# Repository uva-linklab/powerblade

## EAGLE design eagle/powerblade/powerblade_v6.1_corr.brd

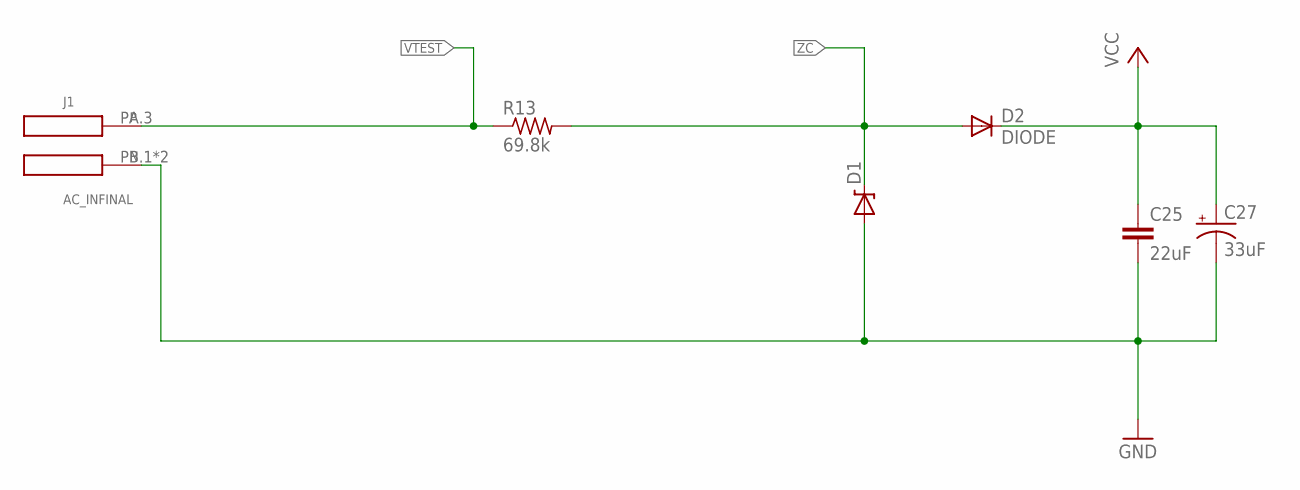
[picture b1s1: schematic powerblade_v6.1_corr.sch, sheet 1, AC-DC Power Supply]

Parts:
C25: 22uF; C0603_SM; DIGIKEY 445-9077-1-ND
C27: 33uF; CPOL0805_SM; DIGIKEY 478-8650-1-ND
D1: ZENERBZT52; BZT52; DIGIKEY BZT52C10T-7DICT-ND
D2: DIODE; BAS521
J1: AC_INFINAL; AC3_FINAL; DIGIKEY ED1649-ND
R13: 69.8k; R1210; DIGIKEY P69.8KAACT-ND

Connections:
GND: C25.2, C27.-, D1.A, J1.PB.1 (N), J1.PB.3 (N); also elsewhere on the board
VCC: C25.1, C27.+, D2.C; also elsewhere on the board
VTEST: J1.PA.3, R13.1; also elsewhere on the board
ZC: D1.C, D2.A, R13.2; also elsewhere on the board

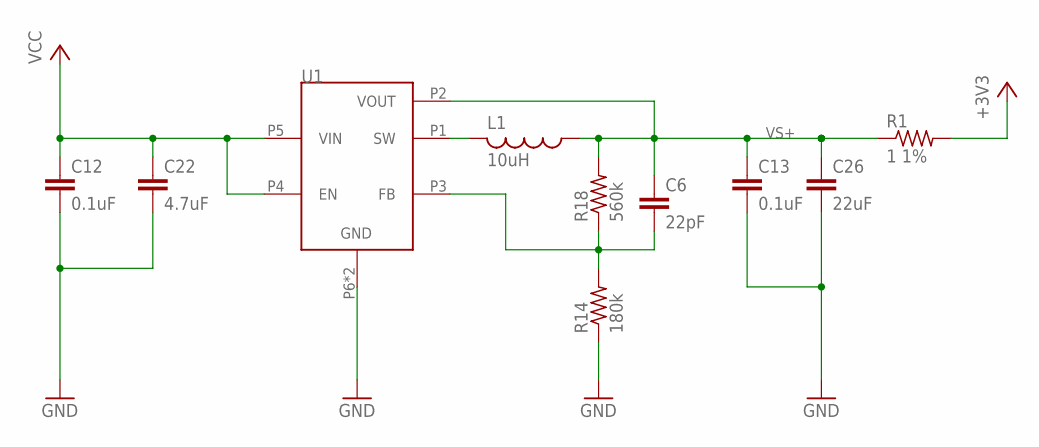
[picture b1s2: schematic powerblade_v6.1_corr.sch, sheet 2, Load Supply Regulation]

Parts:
C6: 22pF; C0402; DIGIKEY 445-1239-1-ND
C12: 0.1uF; C0402; DIGIKEY 445-4952-1-ND
C13: 0.1uF; C0402_SM; DIGIKEY 445-4952-1-ND
C22: 4.7uF; C0402; DIGIKEY 445-8023-1-ND
C26: 22uF; C0603_SM; DIGIKEY 445-9077-1-ND
L1: 10uH; L0805; DIGIKEY 490-4990-1-ND
R1: 1 1%; R0603_SM; DIGIKEY P1.0AJCT-ND
R14: 180k; R0402; DIGIKEY P180KLCT-ND
R18: 560k; R0402; DIGIKEY P560KLCT-ND
U1: TPS62122; WDFN-6

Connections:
+3V3: R1.2; also elsewhere on the board
GND: C12.2, C13.2, C22.2, C26.2, R14.1, U1.P6 (GND), U1.PAD (GND); also elsewhere on the board
unnamed: L1.2, U1.P1 (SW)
unnamed: C6.2, R14.2, R18.1, U1.P3 (FB)
VCC: C12.1, C22.1, U1.P4 (EN), U1.P5 (VIN); also elsewhere on the board
VS+: C6.1, C13.1, C26.1, L1.1, R1.1, R18.2, U1.P2 (VOUT)

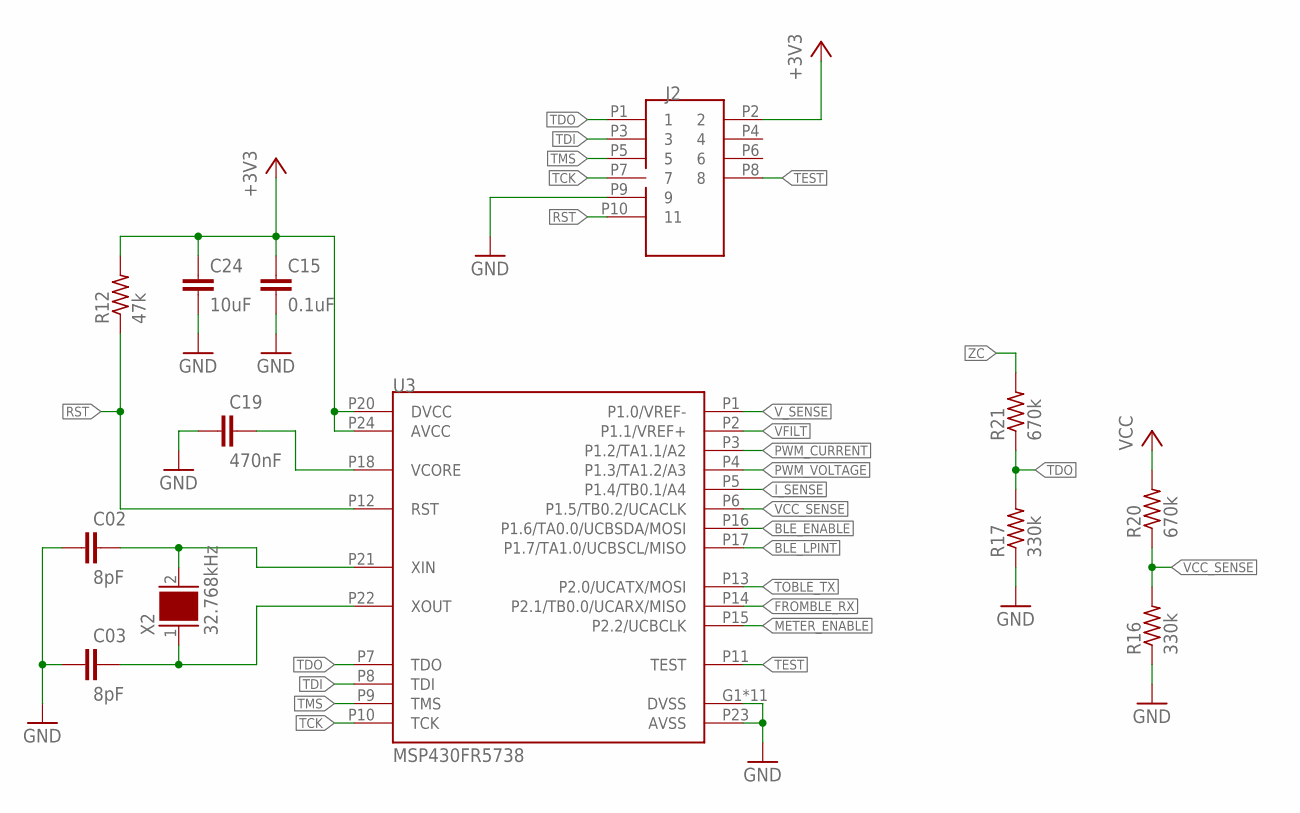
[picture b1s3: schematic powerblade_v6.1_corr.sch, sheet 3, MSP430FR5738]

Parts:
C02, C03: 8pF; C0402; DIGIKEY 445-4890-1-ND
C15: 0.1uF; C0402; DIGIKEY 445-4952-1-ND
C19: 470nF; C0402; DIGIKEY 445-4989-1-ND
C24: 10uF; C0603_SM; DIGIKEY 445-6853-1-ND
J2: JTAG_14PIN_IDC-ND; TC2050-IDC-NL-430-ND; DIGIKEY NP
R12: 47k; R0402; DIGIKEY P47KJCT-ND
R16, R17: 330k; R0402; DIGIKEY P330KLCT-ND
R20, R21: 670k; R0402; DIGIKEY P665KLCT-ND
U3: MSP430FR5738; VQFN-24
X2: 32.768kHz; 0805; DIGIKEY 535-12373-1-ND

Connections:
+3V3: C15.1, C24.1, J2.P2 (2), R12.2, U3.P20 (DVCC), U3.P24 (AVCC); also elsewhere on the board
BLE_ENABLE: U3.P16 (P1.6/TA0.0/UCBSDA/MOSI); also elsewhere on the board
BLE_LPINT: U3.P17 (P1.7/TA1.0/UCBSCL/MISO); also elsewhere on the board
FROMBLE_RX: U3.P14 (P2.1/TB0.0/UCARX/MISO); also elsewhere on the board
GND: C02.1, C03.1, C15.2, C19.1, C24.2, J2.P9 (9), R16.1, R17.1, U3.G1 (DVSS), U3.G2 (DVSS), U3.G3 (DVSS), U3.G4 (DVSS), U3.G5 (DVSS), U3.G6 (DVSS), U3.G7 (DVSS), U3.G8 (DVSS), U3.G9 (DVSS), U3.P19 (DVSS), U3.P23 (AVSS), U3.PAD (DVSS); also elsewhere on the board
I_SENSE: U3.P5 (P1.4/TB0.1/A4); also elsewhere on the board
METER_ENABLE: U3.P15 (P2.2/UCBCLK); also elsewhere on the board
unnamed: C03.2, U3.P22 (XOUT), X2.1
unnamed: C19.2, U3.P18 (VCORE)
unnamed: C02.2, U3.P21 (XIN), X2.2
PWM_CURRENT: U3.P3 (P1.2/TA1.1/A2)
PWM_VOLTAGE: U3.P4 (P1.3/TA1.2/A3)
RST: J2.P10 (11), R12.1, U3.P12 (RST)
TCK: J2.P7 (7), U3.P10 (TCK)
TDI: J2.P3 (3), U3.P8 (TDI)
TDO: J2.P1 (1), R17.2, R21.1, U3.P7 (TDO)
TEST: J2.P8 (8), U3.P11 (TEST)
TMS: J2.P5 (5), U3.P9 (TMS)
TOBLE_TX: U3.P13 (P2.0/UCATX/MOSI); also elsewhere on the board
VCC: R20.2; also elsewhere on the board
VCC_SENSE: R16.2, R20.1, U3.P6 (P1.5/TB0.2/UCACLK)
VFILT: U3.P2 (P1.1/VREF+); also elsewhere on the board
V_SENSE: U3.P1 (P1.0/VREF-); also elsewhere on the board
ZC: R21.2; also elsewhere on the board

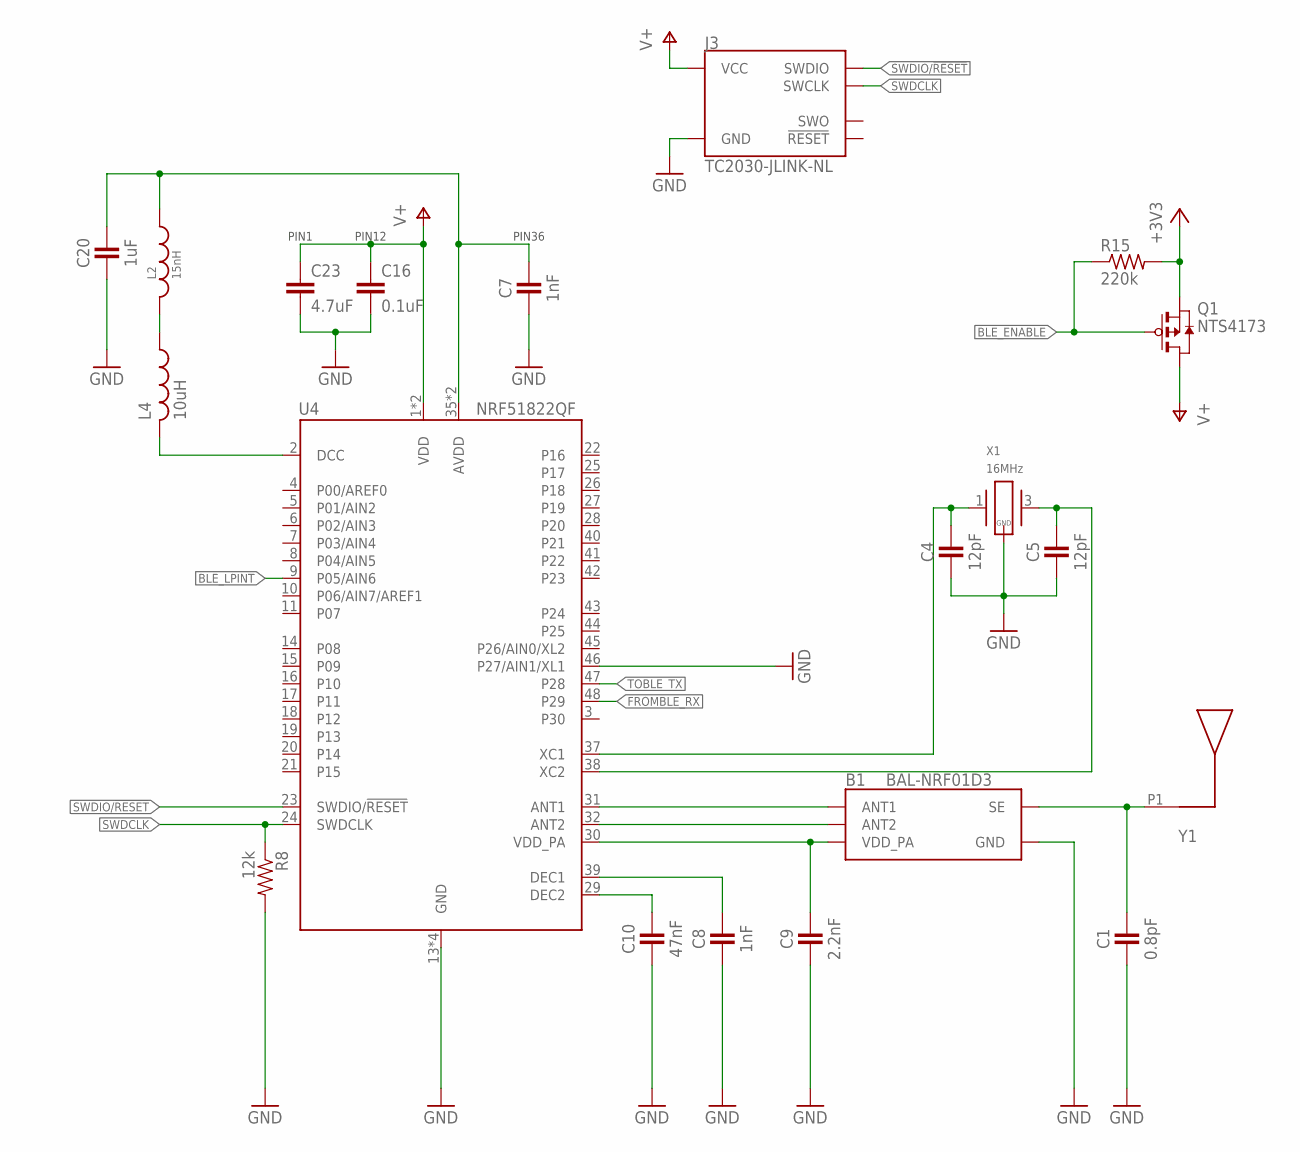
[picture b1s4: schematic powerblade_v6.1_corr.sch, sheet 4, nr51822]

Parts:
B1: BAL-NRF01D3
C1: 0.8pF; 0402_CAP; DIGIKEY 490-6269-1-ND
C4, C5: 12pF; 0402_CAP; DIGIKEY 490-6197-1-ND
C7, C8: 1nF; 0402_CAP; DIGIKEY 490-1303-1-ND
C9: 2.2nF; 0402_CAP; DIGIKEY 490-5419-1-ND
C10: 47nF; 0402_CAP; DIGIKEY 445-1264-1-ND
C16: 0.1uF; C0402; DIGIKEY 445-4952-1-ND
C20: 1uF; 0402_CAP; DIGIKEY 1276-1513-1-ND
C23: 4.7uF; C0402; DIGIKEY 445-5947-1-ND
J3: TC2030-JLINK-NL; TC2030-IDC-NL; DIGIKEY NP
L2: 15nH; 0402_CAP; DIGIKEY 587-1521-1-ND
L4: 10uH; C0603_TN; DIGIKEY 490-4025-1-ND
Q1: NTS4173; SC-70-3
R8: 12k; 0402_RES; DIGIKEY RHM12.0KCDCT-ND
R15: 220k; R0402_SM; DIGIKEY P220KJCT-ND
U4: NRF51822QF; QFN-48-6MM
X1: 16MHz; TXC-8Y; DIGIKEY 887-2003-1-ND
Y1: UREACH_XTEND

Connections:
+3V3: Q1.P2 (S), R15.2; also elsewhere on the board
AVDD: C7.1, C20.1, L2.1, U4.35 (AVDD), U4.36 (AVDD)
BLE_ENABLE: Q1.P1 (G), R15.1; also elsewhere on the board
BLE_LPINT: U4.9 (P05/AIN6); also elsewhere on the board
DCC: L4.2, U4.2 (DCC)
FROMBLE_RX: U4.48 (P29); also elsewhere on the board
GND: B1.GND, C1.2, C4.2, C5.2, C7.2, C8.2, C9.2, C10.2, C16.2, C20.2, C23.2, J3.5 (GND), R8.2, U4.13 (GND), U4.33 (GND), U4.34 (GND), U4.46 (P27/AIN1/XL1), U4.GND, X1.2 (GND), X1.4 (GND); also elsewhere on the board
unnamed: B1.SE, C1.1, Y1.P1
unnamed: B1.ANT1, U4.31 (ANT1)
unnamed: B1.ANT2, U4.32 (ANT2)
unnamed: L2.2, L4.1
unnamed: C4.1, U4.37 (XC1), X1.1
unnamed: C5.1, U4.38 (XC2), X1.3 (2)
unnamed: C8.1, U4.39 (DEC1)
unnamed: C10.1, U4.29 (DEC2)
SWDCLK: J3.4 (SWCLK), R8.1, U4.24 (SWDCLK)
SWDIO/!RESET: J3.2 (SWDIO), U4.23 (SWDIO/!RESET)
TOBLE_TX: U4.47 (P28); also elsewhere on the board
V+: C16.1, C23.1, J3.1 (VCC), Q1.P3 (D), U4.1 (VDD), U4.12 (VDD)
VDD_PA: B1.VCC (VDD_PA), C9.1, U4.30 (VDD_PA)

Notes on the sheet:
PIN12
PIN1
PIN36

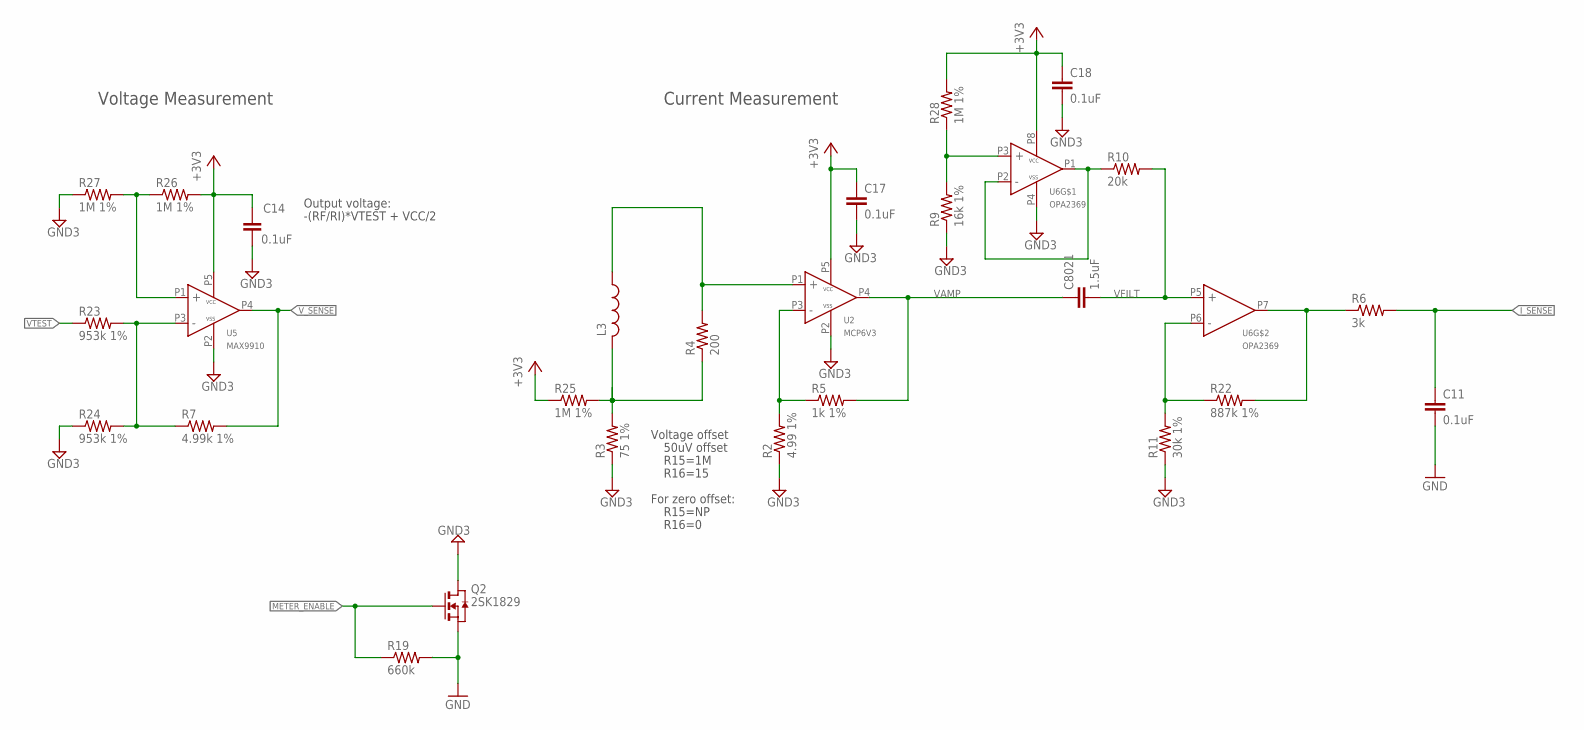
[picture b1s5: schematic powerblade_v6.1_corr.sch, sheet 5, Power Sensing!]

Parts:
C11: 0.1uF; C0402; DIGIKEY 490-10777-1-ND
C14: 0.1uF; 0402_CAP; DIGIKEY 445-4952-1-ND
C17, C18: 0.1uF; C0402; DIGIKEY 445-4952-1-ND
C8021: 1.5uF; C0402; DIGIKEY 445-13815-1-ND
L3: L-USL0805; L0805; DIGIKEY 732-3452-1-ND
Q2: 2SK1829; SC-70-3
R2: 4.99 1%; R0402; DIGIKEY RMCF0402FT4R99CT-ND
R3: 75 1%; R0402; DIGIKEY P75.0LCT-ND
R4: 200; R0402; DIGIKEY P200LCT-ND
R5: 1k 1%; R0402; DIGIKEY P1.00KLCT-ND
R6: 3k; R0402_SM; DIGIKEY P3.00KLCT-ND
R7: 4.99k 1%; R0402; DIGIKEY P4.99KLCT-ND
R9: 16k 1%; R0402; DIGIKEY P16.0KLCT-ND
R10: 20k; R0402; DIGIKEY P20.0KLCT-ND
R11: 30k 1%; R0402; DIGIKEY P30.0KLCT-ND
R19: 660k; R0402; DIGIKEY P665KLCT-ND
R22: 887k 1%; R0402; DIGIKEY P887KLCT-ND
R23, R24: 953k 1%; R0402; DIGIKEY P953KLCT-ND
R25, R26, R28: 1M 1%; R0402; DIGIKEY P1.00MLCT-ND
R27: 1M 1%; R0402_SM; DIGIKEY P1.00MLCT-ND
U2: MCP6V3; SC70-5; DIGIKEY 296-19547-1-ND
U5: MAX9910; SC70-5; DIGIKEY 296-25252-1-ND
U6: OPA2369; SOT-23-8

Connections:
+3V3: C14.1, C17.1, C18.1, R25.1, R26.2, R28.2, U2.P5 (VCC), U5.P5 (VCC), U6.P8 (VCC); also elsewhere on the board
GND: C11.2, Q2.P2 (S), R19.2; also elsewhere on the board
GND3: C14.2, C17.2, C18.2, Q2.P3 (D), R2.1, R3.1, R9.1, R11.1, R24.1, R27.1, U2.P2 (VSS), U5.P2 (VSS), U6.P4 (VSS)
I_SENSE: C11.1, R6.2; also elsewhere on the board
METER_ENABLE: Q2.P1 (G), R19.1; also elsewhere on the board
unnamed: R6.1, R22.2, U6.P7 (OUT)
unnamed: L3.2, R3.2, R4.1, R25.2
unnamed: L3.1, R4.2, U2.P1 (IN+)
unnamed: R26.1, R27.2, U5.P1 (IN+)
unnamed: R7.1, R23.2, R24.2, U5.P3 (IN-)
unnamed: R2.2, R5.1, U2.P3 (IN-)
unnamed: R11.2, R22.1, U6.P6 (IN-)
unnamed: R10.1, U6.P1 (OUT), U6.P2 (IN-)
unnamed: R9.2, R28.1, U6.P3 (IN+)
VAMP: C8021.1, R5.2, U2.P4 (OUT)
VFILT: C8021.2, R10.2, U6.P5 (IN+); also elsewhere on the board
VTEST: R23.1; also elsewhere on the board
V_SENSE: R7.2, U5.P4 (OUT); also elsewhere on the board

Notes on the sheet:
Voltage offset
50uV offset
For zero offset:
R15=NP
R16=0
Current Measurement
Voltage Measurement
Output voltage:
-(RF/RI)*VTEST + VCC/2
R15=1M
R16=15

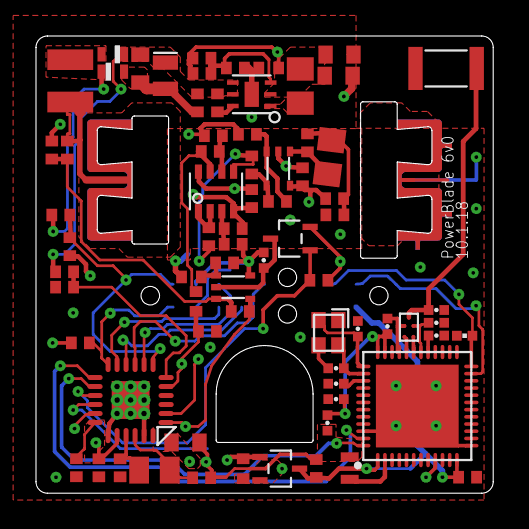
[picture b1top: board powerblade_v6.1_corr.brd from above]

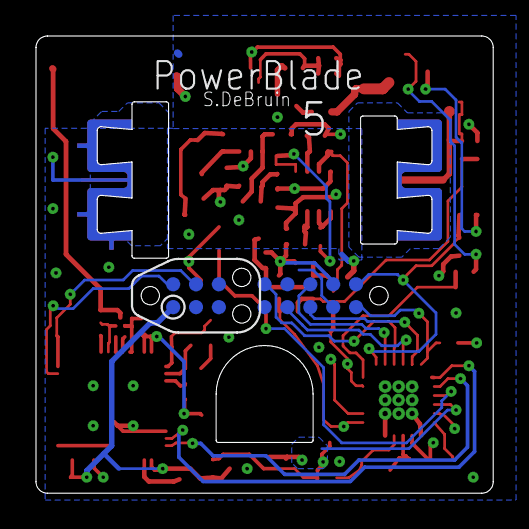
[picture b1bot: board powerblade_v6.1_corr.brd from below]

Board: 4 copper layers, 25.4 x 25.4 mm, 76 parts (2 on the bottom side), 51 nets.

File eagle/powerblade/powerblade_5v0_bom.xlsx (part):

Quantity | Part | Value | Device | Package | Description | Distributor | Dist Part # | Type | Alternate | Alternate2 | Mouser | Each 750 | Total 750 | Each 1000 | Total 1000
1 | B1 | BAL-NRF01D3 | BAL-NRF01D3 | BAL-NRF01D3 | 50 ohm nominal input / conjugate match balun to nRF51422-QFAA, |  | 497-13637-1-ND | BGA | 497-13637-1-ND |  |  | 0.42132999999999998 | 0.42132999999999998 | 0.3296 | 0.3296 | 0.3296
1 | C1 | 0.8pF | CAPACITOR | 0402_CAP | 0402 Capacitor |  | 490-6269-1-ND | smt | 490-6269-1-ND |  |  | 3.9039999999999998E-2 | 3.9039999999999998E-2 |  | 0 | 3.9039999999999998E-2
2 | C2, C3 | 8pF | C-EUC0402 | C0402 | CAPACITOR, European symbol |  | 445-4890-1-ND | smt | 445-4890-1-ND |  |  | 1.8110000000000001E-2 | 3.6220000000000002E-2 |  | 0 | 3.6220000000000002E-2
2 | C4, C5 | 12pF | CAPACITOR | 0402_CAP | 0402 Capacitor |  | 490-6197-1-ND | smt | 490-6196-1-ND | 490-8078-6-ND |  | 5.5300000000000002E-2 | 0.1106 |  | 0 | 0.1106
1 | C6 | 22pF | C-EUC0402 | C0402 | CAPACITOR, European symbol |  | 445-1239-1-ND | smt | 445-1239-1-ND | 720-1609-6-ND |  | 0.37364999999999998 | 0.37364999999999998 | 0.32072000000000001 | 0.32072000000000001 | 0.32072000000000001 | y
2 | C7, C8 | 1nF | CAPACITOR | 0402_CAP | 0402 Capacitor |  | 490-1303-1-ND | smt | 490-1303-1-ND | 490-4761-6-ND |  | 1.6060000000000001E-2 | 3.2120000000000003E-2 |  | 0 | 3.2120000000000003E-2 | y
1 | C9 | 2.2nF | CAPACITOR | 0402_CAP | 0402 Capacitor |  | 490-5419-1-ND | smt | 490-5419-1-ND | 399-1033-6-ND |  | 0.18593000000000001 | 0.18593000000000001 | 2.955E-2 | 2.955E-2 | 2.955E-2
1 | C10 | 47nF | CAPACITOR | 0402_CAP | 0402 Capacitor |  | 445-1264-1-ND | smt |  |  |  | 0.03 | 0.03 |  | 0 | 0.03
1 | C11, C12, C13, C14, C15, C16, C17, C18 | 0.1uF | C-EUC0402 | C0402 | CAPACITOR, European symbol |  | 490-10777-1-ND | smt | 399-7761-6-ND | 1276-1509-6-ND |  | 0.18593000000000001 | 0.18593000000000001 | 0.10920000000000001 | 0.10920000000000001 | 0.10920000000000001
1 | C19 | 470nF | C-EUC0402 | C0402 | CAPACITOR, European symbol |  | 445-4989-1-ND | smt | 445-13864-1-ND | 587-1455-6-ND |  | 5.9810000000000002E-2 | 5.9810000000000002E-2 |  | 0 | 5.9810000000000002E-2
1 | C20 | 1uF | CAPACITOR | 0402_CAP | 0402 Capacitor |  | 1276-1513-1-ND | smt | 1276-1513-1-ND | 587-2477-6-ND |  | 5.9810000000000002E-2 | 5.9810000000000002E-2 |  | 0 | 5.9810000000000002E-2 | y
1 | C21 | 1.5uF | C-EUC0402 | C0402 | CAPACITOR, European symbol |  | 445-13815-1-ND | smt |  |  |  | 0.11284 | 0.11284 | 9.7559999999999994E-2 | 9.7559999999999994E-2 | 9.7559999999999994E-2
1 | C22, C23 | 4.7uF | C-EUC0402 | C0402 | CAPACITOR, European symbol |  | 445-8023-1-ND | smt | 445-13820-1-ND | 490-10984-6-ND |  | 0.13028999999999999 | 0.13028999999999999 | 0.10915 | 0.10915 | 0.10915
1 | C24 | 10uF | C-EUC0603_SM | C0603_SM | CAPACITOR, European symbol |  | 445-6853-1-ND | smt | 490-10987-6-ND |  |  | 0.15487999999999999 | 0.15487999999999999 | 0.12991 | 0.12991 | 0.12991 | y
2 | C25, C26 | 22uF | C-EUC0603_SM | C0603_SM | CAPACITOR, European symbol |  | 445-9077-1-ND | smt |  |  |  | 0.17573 | 0.35145999999999999 | 0.17455999999999999 | 0.34911999999999999 | 0.34911999999999999 | y
1 | C27 | 33uF | CPOL-US0805_SM | CPOL0805_SM | POLARIZED CAPACITOR, American symbol |  | 478-8650-1-ND | smt | 478-8650-1-ND |  |  | 0.45773000000000003 | 0.45773000000000003 | 0.20355000000000001 | 0.20355000000000001 | 0.20355000000000001
1 | D1 | ZENERBZT52 | ZENERBZT52 | BZT52 |  |  | BZT52C10T-7DICT-ND | smt |  |  |  | 8.2290000000000002E-2 | 8.2290000000000002E-2 |  | 0 | 8.2290000000000002E-2 | y
1 | D2 | DIODE | DIODE | BAS521 |  |  | BAS521-7DICT-ND | smt |  |  |  | 0.12404999999999999 | 0.12404999999999999 | 8.5010000000000002E-2 | 8.5010000000000002E-2 | 8.5010000000000002E-2 | y
4 | J1 | Ultra Low Profile Spring Pin | Ultra Low Profile Spring Pin | Ultra Low Profile Spring Pin |  |  | ED1649-ND | smt | ED1649-ND |  |  | 0.20355000000000001 | 0.81420000000000003 | 0.20355000000000001 | 0.81420000000000003 | 0.81420000000000003 | y
1 | L1 | 10uH | L-USL0805 | L0805 | INDUCTOR, American symbol |  | 490-4990-1-ND | smt |  |  |  | 0.23416999999999999 | 0.23416999999999999 | 0.17921999999999999 | 0.17921999999999999 | 0.17921999999999999 | y
1 | L2 | 15nH | INDUCTOR0402 | 0402_CAP |  |  | 587-1521-1-ND | smt |  |  |  | 2.5159999999999998E-2 | 2.5159999999999998E-2 |  | 0 | 2.5159999999999998E-2 | y
1 | L3 |  | L-USL0805 | L0805 | INDUCTOR, American symbol |  | 732-3452-1-ND | smt |  |  | 710-744760410A | 0.34433000000000002 | 0.34433000000000002 | 0.313 | 0.313 | 0.313 | y
1 | L4 | 10uH | L-USL0603_TN | C0603_TN | INDUCTOR, American symbol |  | 490-4025-1-ND | smt | 535-12249-1-ND |  |  | 8.3799999999999999E-2 | 8.3799999999999999E-2 |  | 0 | 8.3799999999999999E-2 | y
1 | Q1 | NTS4173 | NTS4173 | SC-70-3 |  |  | NTS4173PT1GOSCT-ND | smt | 785-1085-6-ND |  |  | 0.18643999999999999 | 0.18643999999999999 | 0.14323 | 0.14323 | 0.14323 | y
1 | Q2 | 2SK1829 | 2SK1829 | SC-70-3 |  |  | 2SK1829TE85LFCT-ND | smt | 1727-1288-6-ND |  |  | 0.16331999999999999 | 0.16331999999999999 | 0.12545000000000001 | 0.12545000000000001 | 0.12545000000000001
1 | R1 | 1 1% | R-US_R0603_SM | R0603_SM | RESISTOR, American symbol |  | P1.0AJCT-ND | smt | P1.0AJCT-ND |  |  | 4.5370000000000001E-2 | 4.5370000000000001E-2 |  | 0 | 4.5370000000000001E-2
1 | R2 | 4.99 1% | R-US_R0402 | R0402 | RESISTOR, American symbol |  | RMCF0402FT4R99CT-ND | smt | RMCF0402FT4R99CT-ND |  |  | 6.7999999999999996E-3 | 6.7999999999999996E-3 |  | 0 | 6.7999999999999996E-3
1 | R3 | 75 1% | R-US_R0402 | R0402 | RESISTOR, American symbol |  | P75.0LCT-ND | smt | P75.0LCT-ND |  |  | 2.6929999999999999E-2 | 2.6929999999999999E-2 |  | 0 | 2.6929999999999999E-2
1 | R4 | 200 | R-US_R0402 | R0402 | RESISTOR, American symbol |  | P200LCT-ND | smt | P200LCT-ND |  |  | 2.6929999999999999E-2 | 2.6929999999999999E-2 |  | 0 | 2.6929999999999999E-2
1 | R5 | 1k 1% | R-US_R0402 | R0402 | RESISTOR, American symbol |  | P1.00KLCT-ND | smt | P1.00KLCT-ND |  |  | 2.6929999999999999E-2 | 2.6929999999999999E-2 |  | 0 | 2.6929999999999999E-2
1 | R6 | 3k | R-US_R0402_SM | R0402_SM | RESISTOR, American symbol |  | P3.00KLCT-ND | smt | P3.00KLCT-ND |  |  | 2.6929999999999999E-2 | 2.6929999999999999E-2 |  | 0 | 2.6929999999999999E-2
1 | R7 | 4.99k 1% | R-US_R0402 | R0402 | RESISTOR, American symbol |  | P4.99KLCT-ND | smt | P4.99KLCT-ND |  |  | 2.6929999999999999E-2 | 2.6929999999999999E-2 |  | 0 | 2.6929999999999999E-2
1 | R8 | 12k | RESISTOR | 0402_RES | Resistor |  | RHM12.0KCDCT-ND | smt | RHM12.0KCDCT-ND | 311-12.0KLRDKR-ND |  | 1.473E-2 | 1.473E-2 |  | 0 | 1.473E-2
1 | R9 | 16k 1% | R-US_R0402 | R0402 | RESISTOR, American symbol |  | P16.0KLCT-ND | smt | P16.0KLCT-ND |  |  | 2.6929999999999999E-2 | 2.6929999999999999E-2 |  | 0 | 2.6929999999999999E-2
1 | R10 | 20k | R-US_R0402 | R0402 | RESISTOR, American symbol |  | P20.0KLCT-ND | smt | P20.0KLCT-ND |  |  | 2.6929999999999999E-2 | 2.6929999999999999E-2 |  | 0 | 2.6929999999999999E-2
1 | R11 | 30k 1% | R-US_R0402 | R0402 | RESISTOR, American symbol |  | P30.0KLCT-ND | smt | P30.0KLCT-ND |  |  | 2.6929999999999999E-2 | 2.6929999999999999E-2 |  | 0 | 2.6929999999999999E-2
1 | R12 | 47k | R-US_R0402 | R0402 | RESISTOR, American symbol |  | P47KJCT-ND | smt | P47KJCT-ND |  |  | 2.104E-2 | 2.104E-2 |  | 0 | 2.104E-2
1 | R13 | 69.8k | R-US_R1210 | R1210 | RESISTOR, American symbol |  | P69.8KAACT-ND | smt | P69.8KAACT-ND |  |  | 0.11244 | 0.11244 |  | 0 | 0.11244
1 | R14 | 180k | R-US_R0402 | R0402 | RESISTOR, American symbol |  | P180KLCT-ND | smt | P180KLCT-ND |  |  | 2.6929999999999999E-2 | 2.6929999999999999E-2 |  | 0 | 2.6929999999999999E-2
1 | R15 | 220k | R-US_R0402_SM | R0402_SM | RESISTOR, American symbol |  | P220KJCT-ND | smt | P220KJCT-ND |  |  | 2.104E-2 | 2.104E-2 |  | 0 | 2.104E-2
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
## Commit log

2018-09-10 more room

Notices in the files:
parts and their libraries:
SparkFun-Aesthetics: Licensing: CC v3.0 Share-Alike You are welcome to use this library for commercial purposes.
